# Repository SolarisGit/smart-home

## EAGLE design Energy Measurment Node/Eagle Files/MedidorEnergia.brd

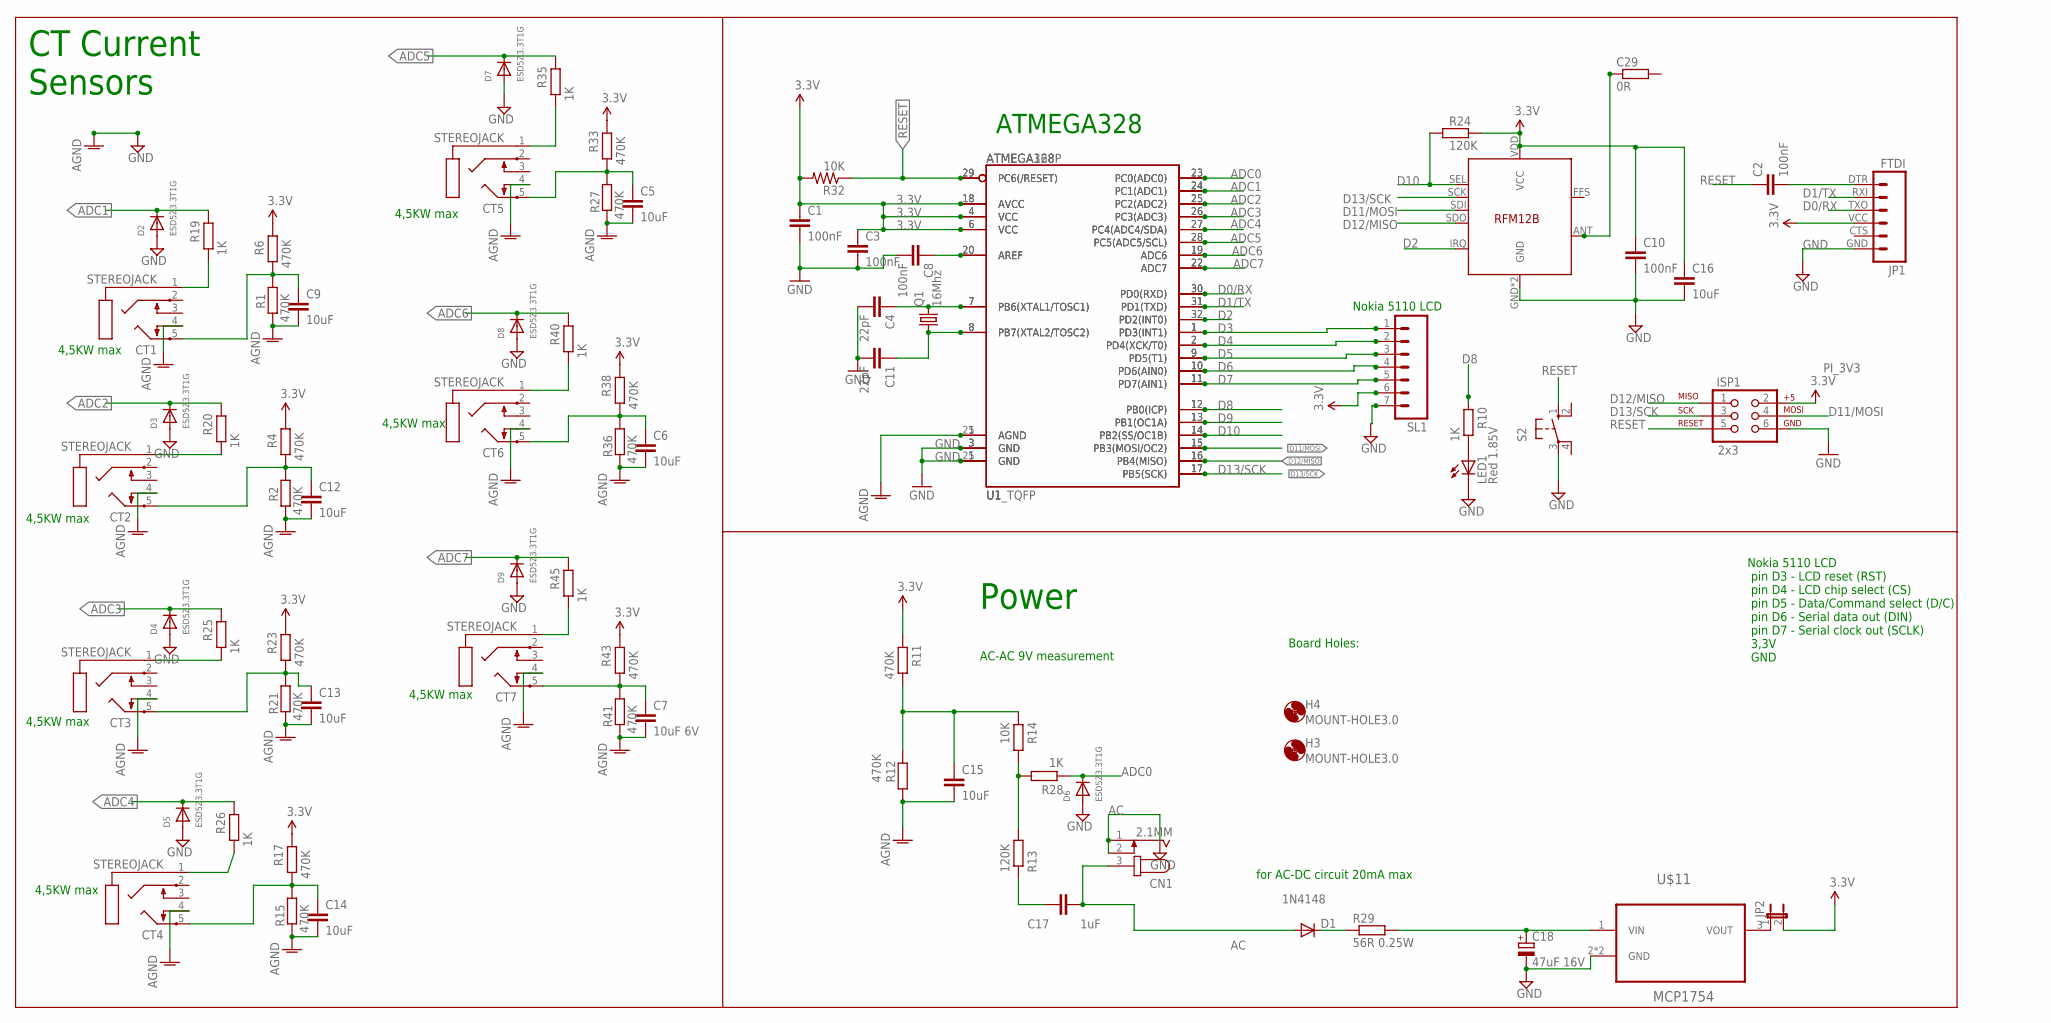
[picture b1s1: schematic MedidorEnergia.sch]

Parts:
C1, C2, C3, C8, C10: 100nF; C0603; MPN CC0603MRY5V9BB104
C4, C11: 22pF; C0603; MPN CC0603JRNPO9BN220
C5, C6, C9, C12, C13, C14: 10uF; C0805; MPN TAJC106K025RNJ
C7: 10uF 6V; C0805; MPN TAJC106K025RNJ
C15, C16: 10uF; C1206; MPN TAJC106K025RNJ
C17: 1uF; C0805; MPN 08055C104KAT2A
C18: 47uF 16V; PANASONIC_D; MPN EEEFC1C470AP
C29: 0R; R0603
CN1: 2.1MM; SPC4077; MPN SPC21364
CT1, CT2, CT3, CT4, CT5, CT6, CT7: STEREOJACK; STX3100; MPN FC68131
D1: 1N4148; SOD-323; MPN 1N4148WS.
D2, D3, D4, D5, D6, D7, D8, D9: ESD5Z3.3T1G; SOD-523; MPN ESD5Z3.3T1G
H3, H4: MOUNT-HOLE3.0; 3,0
ISP1: 2x3; 2X3; MPN M20-9970346
JP1: FTDI; FTDI_BASIC; MPN 2212S-10SG-85
JP2: JUMPER-2PTH_LOCK; 1X02_LOCK
LED1: Red 1.85V; CHIP-LED0805; MPN MCL-S270SRC
Q1: 16Mhz; HC49/S; MPN HC49SM-3.6864-30-50-60-16-ATF
R1, R2, R4, R6, R11, R12, R15, R17, R21, R23, R27, R33, R36, R38, R41, R43: 470K; R0603; MPN RE0603DR-07470KL
R10, R19, R20, R25, R26, R28, R35, R40, R45: 1K; R0603; MPN PCF0603R-1K0BT1
R13, R24: 120K; R0603; MPN RT0603FRE07120KL
R14, R32: 10K; R0603; MPN PCF0603R-10KBT1
R29: 56R 0.25W; R1206; MPN CRCW120656R0JNEA
S2: 10-XX; B3F-10XX
SL1: M07; 07P; MPN M20-9991045
U1: ATMEGA168; TQFP32-08
U1_TQFP: ATMEGA328P; TQFP32-08
U$11: MCP1754; SOT89; MPN MCP1754ST-3302E/MB
U$14: RFM12B

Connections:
3.3V: C1.1, C3.1, C10.1, C16.1, ISP1.2, JP1.VCC (4), JP2.2, R4.2, R6.2, R11.2, R17.2, R23.2, R24.2, R32.2, R33.2, R38.2, R43.2, SL1.6, U1.4 (VCC), U1.6 (VCC), U1.18 (AVCC), U1_TQFP.4 (VCC), U1_TQFP.6 (VCC), U1_TQFP.18 (AVCC), U$14.VDD (VCC)
AC: C17.2, CN1.3, D1.2 (A)
ADC0: D6.K (C), R28.1, U1.23 (PC0(ADC0)), U1_TQFP.23 (PC0(ADC0))
ADC1: D2.K (C), R19.2, U1.24 (PC1(ADC1)), U1_TQFP.24 (PC1(ADC1))
ADC2: D3.K (C), R20.2, U1.25 (PC2(ADC2)), U1_TQFP.25 (PC2(ADC2))
ADC3: D4.K (C), R25.2, U1.26 (PC3(ADC3)), U1_TQFP.26 (PC3(ADC3))
ADC4: D5.K (C), R26.2, U1.27 (PC4(ADC4/SDA)), U1_TQFP.27 (PC4(ADC4/SDA))
ADC5: D7.K (C), R35.2, U1.28 (PC5(ADC5/SCL)), U1_TQFP.28 (PC5(ADC5/SCL))
ADC6: D8.K (C), R40.2, U1.19 (ADC6), U1_TQFP.19 (ADC6)
ADC7: D9.K (C), R45.2, U1.22 (ADC7), U1_TQFP.22 (ADC7)
AGND: C5.2, C6.2, C7.2, C9.2, C12.2, C13.2, C14.2, C15.2, CT1.4, CT2.4, CT3.4, CT4.4, CT5.4, CT6.4, CT7.4, R1.2, R2.2, R12.1, R15.2, R21.2, R27.2, R36.2, R41.2, U1.5 (AGND), U1_TQFP.21 (AGND)
D0/RX: JP1.TXO (3), U1.30 (PD0(RXD)), U1_TQFP.30 (PD0(RXD))
D1/TX: JP1.RXI (2), U1.31 (PD1(TXD)), U1_TQFP.31 (PD1(TXD))
D2: U1.32 (PD2(INT0)), U1_TQFP.32 (PD2(INT0)), U$14.IRQ
D3: SL1.1, U1.1 (PD3(INT1)), U1_TQFP.1 (PD3(INT1))
D4: SL1.2, U1.2 (PD4(XCK/T0)), U1_TQFP.2 (PD4(XCK/T0))
D5: SL1.3, U1.9 (PD5(T1)), U1_TQFP.9 (PD5(T1))
D6: SL1.4, U1.10 (PD6(AIN0)), U1_TQFP.10 (PD6(AIN0))
D7: SL1.5, U1.11 (PD7(AIN1)), U1_TQFP.11 (PD7(AIN1))
D8: R10.2, U1.12 (PB0(ICP)), U1_TQFP.12 (PB0(ICP))
D9: U1.13 (PB1(OC1A)), U1_TQFP.13 (PB1(OC1A))
D10: R24.1, U1.14 (PB2(SS/OC1B)), U1_TQFP.14 (PB2(SS/OC1B)), U$14.SEL
D11/MOSI: ISP1.4, U1.15 (PB3(MOSI/OC2)), U1_TQFP.15 (PB3(MOSI/OC2)), U$14.SDI
D12/MISO: ISP1.1, U1.16 (PB4(MISO)), U1_TQFP.16 (PB4(MISO)), U$14.SDO
D13/SCK: ISP1.3, U1.17 (PB5(SCK)), U1_TQFP.17 (PB5(SCK)), U$14.SCK
GND: C1.2, C3.2, C4.2, C8.2, C10.2, C11.2, C16.2, C18.-, CN1.1, CN1.2, D2.A, D3.A, D4.A, D5.A, D6.A, D7.A, D8.A, D9.A, ISP1.6, JP1.GND (6), LED1.C, S2.3, SL1.7, U1.3 (GND), U1.21 (GND), U1_TQFP.3 (GND), U1_TQFP.5 (GND), U$11.2 (GND), U$11.2.1 (GND), U$14.GND, U$14.P$12 (GND)
unnamed: C4.1, Q1.2, U1.7 (PB6(XTAL1/TOSC1)), U1_TQFP.7 (PB6(XTAL1/TOSC1))
unnamed: CT1.1, R19.1
unnamed: C13.1, CT3.5, R21.1, R23.1
unnamed: R13.2, R14.1, R28.2
unnamed: JP2.1, U$11.3 (VOUT)
unnamed: C18.+, R29.2, U$11.1 (VIN)
unnamed: C17.1, R13.1
unnamed: CT4.1, R26.1
unnamed: C11.1, Q1.1, U1.8 (PB7(XTAL2/TOSC2)), U1_TQFP.8 (PB7(XTAL2/TOSC2))
unnamed: CT2.1, R20.1
unnamed: C29.1, U$14.ANT
unnamed: D1.1 (C), R29.1
unnamed: CT3.1, R25.1
unnamed: C5.1, CT5.5, R27.1, R33.1
unnamed: CT5.1, R35.1
unnamed: C8.1, U1.20 (AREF), U1_TQFP.20 (AREF)
unnamed: C6.1, CT6.5, R36.1, R38.1
unnamed: CT6.1, R40.1
unnamed: C2.2, JP1.DTR (1)
unnamed: C7.1, CT7.5, R41.1, R43.1
unnamed: CT7.1, R45.1
unnamed: C12.1, CT2.5, R2.1, R4.1
unnamed: C15.1, R11.1, R12.2, R14.2
unnamed: C14.1, CT4.5, R15.1, R17.1
unnamed: C9.1, CT1.5, R1.1, R6.1
unnamed: LED1.A, R10.1
RESET: C2.1, ISP1.5, R32.1, S2.1 (S), U1.29 (PC6(/RESET)), U1_TQFP.29 (PC6(/RESET))

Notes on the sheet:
AC-AC 9V measurement
for AC-DC circuit 20mA max
Power
CT Current Sensors
ATMEGA328
Nokia 5110 LCD pin D3 - LCD reset (RST) pin D4 - LCD chip select (CS) pin D5 - Data/Command select (D/C) pin D6 - Serial data out (DIN) pin D7 - Serial clock out (SCLK) 3,3V GND
Nokia 5110 LCD
4,5KW max
Board Holes:

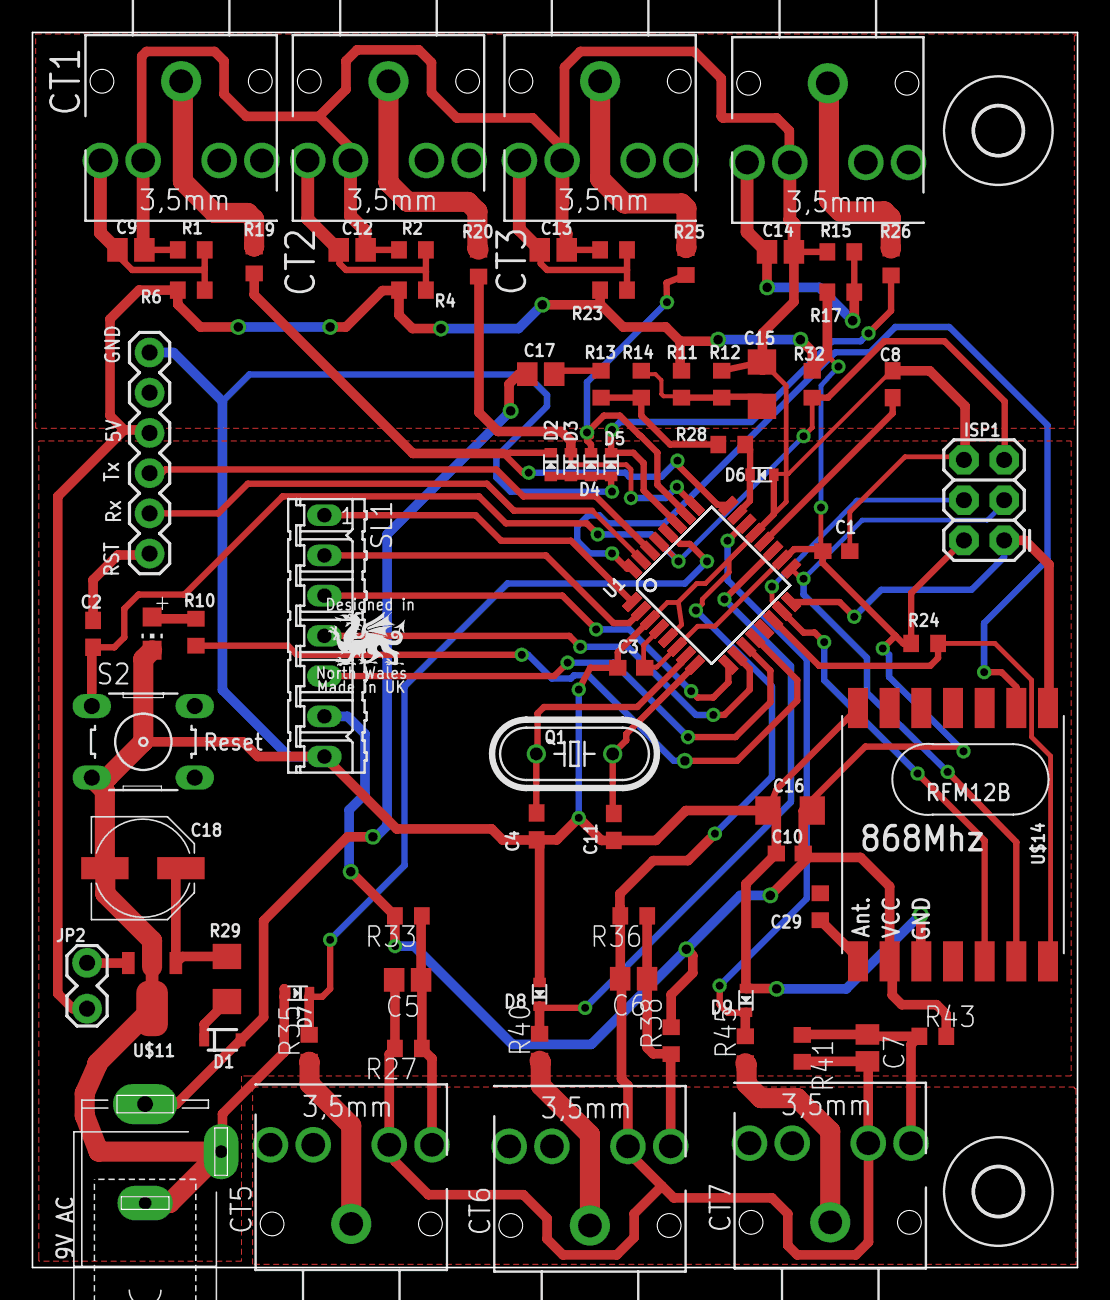
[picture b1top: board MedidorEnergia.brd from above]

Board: 2 copper layers, 66.0 x 78.0 mm, 79 parts (0 on the bottom side), 53 nets.

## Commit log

2018-01-31 Añadido nuevo Nodo para iluminar la entrada mediante una Lamp

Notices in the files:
parts and their libraries:
SparkFun-DigitalIC: Licensing: CC v3.0 Share-Alike You are welcome to use this library for commercial purposes.
microbuilder: This work is placed in the public domain, and may be freely used for commercial and non-commercial work with the following conditions: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
